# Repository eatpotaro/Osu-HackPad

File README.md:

# Osu-HackPad
Hackpad for blueprint run by Hack Club

# Features
- 4 keys used for 4K osu!mania and osu!
- 0.91 inch OLED display to display recent keypresses
- KMK support

# How to use
After uploading the required arduino code, simply run and use! You may need to rebind the keys in Osu! to make sure they are correct. 
 
# CAD Model
Designed using Fusion360. 
Here are some images of the plate, the case, both together, and with pcb

# PCB
Designed using KiCAD. I'm quite happy with the routing on the PCB

# Pictures
Pictures of finished product

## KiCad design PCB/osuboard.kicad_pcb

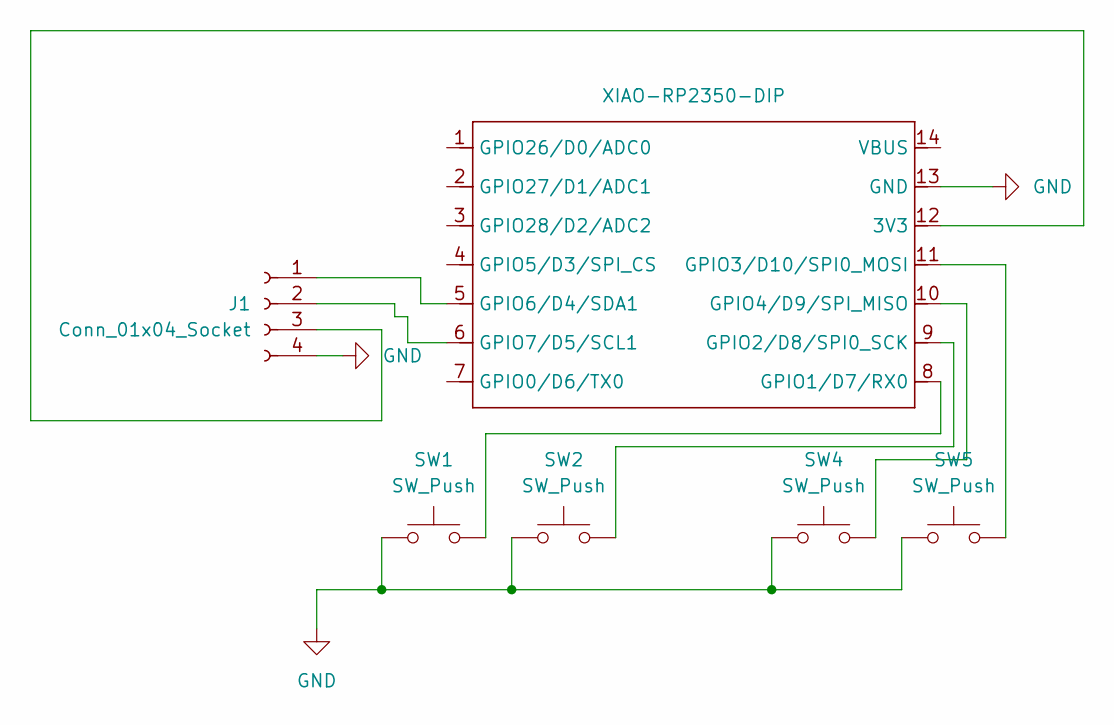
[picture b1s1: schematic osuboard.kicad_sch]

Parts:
J1: Conn_01x04_Socket; NS-Tech_Grove_1x04_P2mm_Vertical
SW1, SW2, SW4, SW5: SW_Push; SW_Cherry_MX_1.00u_PCB
U1: XIAO-RP2350-DIP; XIAO-RP2040-DIP

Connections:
GND: J1.4, SW1.1, SW2.1, SW4.1, SW5.1, U1.13 (GND)
unnamed: J1.1, U1.5 (GPIO6/D4/SDA1)
unnamed: J1.2, U1.6 (GPIO7/D5/SCL1)
unnamed: J1.3, U1.12 (3V3)
unnamed: SW1.2, U1.8 (GPIO1/D7/RX0)
unnamed: SW2.2, U1.9 (GPIO2/D8/SPI0_SCK)
unnamed: SW5.2, U1.11 (GPIO3/D10/SPI0_MOSI)
unnamed: SW4.2, U1.10 (GPIO4/D9/SPI_MISO)

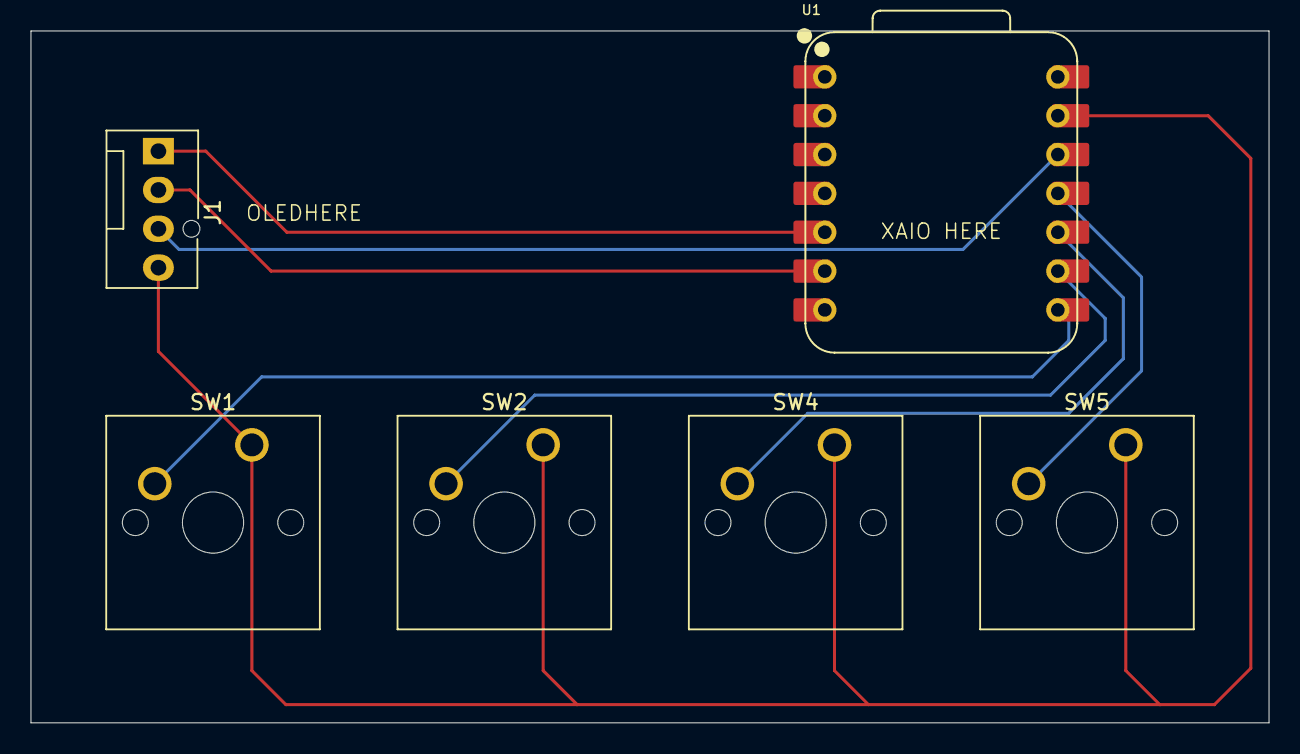
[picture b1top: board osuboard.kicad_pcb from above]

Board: 2 copper layers, 81.0 x 45.2 mm, 6 parts (0 on the bottom side), 8 nets.

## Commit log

2026-01-23 add CAD and KiCAD files for the case and pcbs
2026-01-23 README update
2026-01-23 added pictures in readme
2026-01-23 add firmware kmk
2026-01-23 add firmware real
2026-01-24 added pcb image in render
2026-01-24 add new version of CAD
2026-01-24 Rename osupad.3mf to osupadfullassembly.3mf
2026-01-24 add .step files
2026-01-24 add new PCB file
2026-02-22 upload finshed code
2026-02-23 add images
2026-03-19 add seperate BOM file
2026-03-19 add osupad .f3d full
2026-03-19 Rename osupad.f3d to osupadfull.f3d
2026-03-19 Rename BoM.csv to BOM.csv
